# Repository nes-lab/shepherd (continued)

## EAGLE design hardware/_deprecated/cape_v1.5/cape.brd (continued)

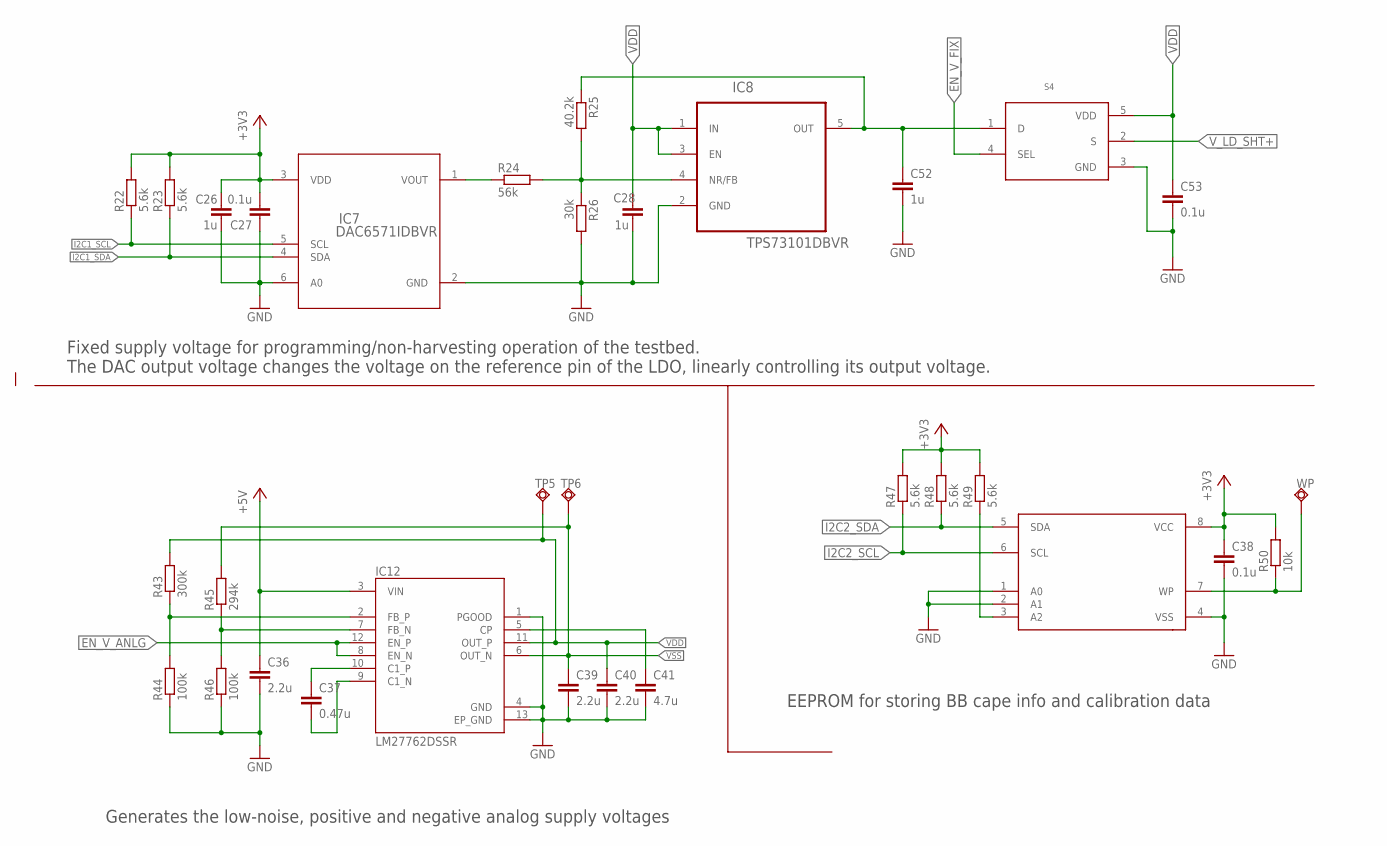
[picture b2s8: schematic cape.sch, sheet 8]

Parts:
C26, C28, C52: 1u; CAPC1608X95
C27, C38, C53: 0.1u; CAPC1005X55
C36, C39, C40: 2.2u; CAPC2012X145
C37: 0.47u; CAPC1608X95
C41: 4.7u; CAPC2012X145
IC7: DAC6571IDBVR
IC8: TPS73101DBVR; SOT95P280X145-5N
IC11: CAT24C256WI-GT3; SO08
IC12: LM27762DSSR; VREG_LM27762DSSR
R22, R23, R47, R48, R49: 5.6k; RESC1005X40
R24: 56k; RESC1005X40
R25: 40.2k; RESC1005X40
R26: 30k; RESC1005X40
R43: 300k; RESC1005X40
R44, R46: 100k; RESC1005X40
R45: 294k; RESC1005X40
R50: 10k; RESC1005X40
S4: TMUX1101DCK; DCK5
TP5, TP6: TPSQTP06R; TP06R
WP: TPSQTP06R; TP06R

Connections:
+3V3: C26.1, C27.2, C38.1, IC7.3 (VDD), IC11.8 (VCC), R22.2, R23.2, R47.2, R48.2, R49.2, R50.2; also elsewhere on the board
+5V: C36.1, IC12.3 (VIN); also elsewhere on the board
EN_V_ANLG: IC12.8 (EN_N), IC12.12 (EN_P); also elsewhere on the board
EN_V_FIX: S4.4 (SEL); also elsewhere on the board
GND: C26.2, C27.1, C28.2, C36.2, C38.2, C39.2, C40.2, C41.2, C52.2, C53.2, IC7.2 (GND), IC7.6 (A0), IC8.2 (GND), IC11.1 (A0), IC11.2 (A1), IC11.4 (VSS), IC12.1 (PGOOD), IC12.4 (GND), IC12.13 (EP_GND), R26.2, R44.1, R46.1, S4.3 (GND); also elsewhere on the board
I2C1_SCL: IC7.5 (SCL), R22.1; also elsewhere on the board
I2C1_SDA: IC7.4 (SDA), R23.1; also elsewhere on the board
I2C2_SCL: IC11.6 (SCL), R47.1; also elsewhere on the board
I2C2_SDA: IC11.5 (SDA), R48.1; also elsewhere on the board
unnamed: C52.1, IC8.5 (OUT), R25.1, S4.1 (D)
unnamed: IC8.4 (NR/FB), R24.2, R25.2, R26.1
unnamed: IC12.2 (FB_P), R43.1, R44.2
unnamed: IC7.1 (VOUT), R24.1
unnamed: IC11.7 (WP), R50.1, WP.TP
unnamed: IC12.7 (FB_N), R45.1, R46.2
unnamed: IC11.3 (A2), R49.1
unnamed: C41.1, IC12.5 (CP)
unnamed: C37.2, IC12.9 (C1_N)
unnamed: C37.1, IC12.10 (C1_P)
VDD: C28.1, C40.1, C53.1, IC8.1 (IN), IC8.3 (EN), IC12.11 (OUT_P), R43.2, S4.5 (VDD), TP5.TP; also elsewhere on the board
VSS: C39.1, IC12.6 (OUT_N), R45.2, TP6.TP; also elsewhere on the board
V_LD_SHT+: S4.2 (S); also elsewhere on the board

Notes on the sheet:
Fixed supply voltage for programming/non-harvesting operation of the testbed. The DAC output voltage changes the voltage on the reference pin of the LDO, linearly controlling its output voltage.
Generates the low-noise, positive and negative analog supply voltages
EEPROM for storing BB cape info and calibration data

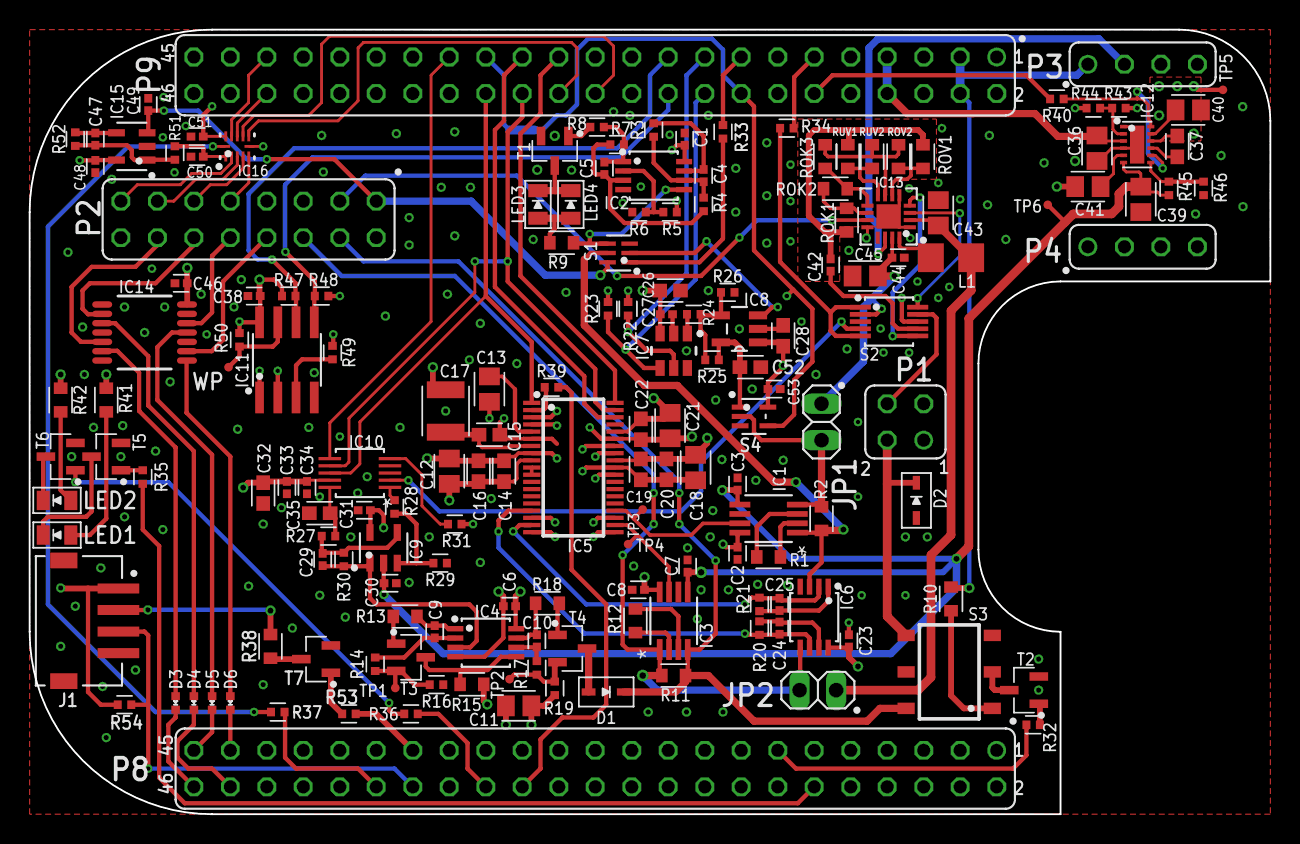
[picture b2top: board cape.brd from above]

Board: 4 copper layers, 86.4 x 54.6 mm, 171 parts (0 on the bottom side), 134 nets.

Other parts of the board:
U$1, U$2, U$3: REFMARK

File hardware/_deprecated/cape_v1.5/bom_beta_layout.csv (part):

"BILL OF MATERIAL WITH BETA STOCK, GROUPED BY VALUES, AS OF 09.10.2015",,,,,,,,,,,,,,,,,,
Part,Value,Device,Package,Description,Description2,Qty,Place_YES/NO,Povided_by_customer_YES/NO,Distributor,Ordernumber,Weblink,Remarks_customer,Unit_price,Total_price,REMARKS_BETA,OPTION1,OPTION2,OPTION3
"C1, C2, C3, C6, C7, C8, C23, C27, C30, C31, C38, C45, C46, C48, C51",0.1u,C_SMD0402,CAPC1005X55, , ,15,YES,NO,Beta,7235228,http://de.rs-online.com/web/p/ceramic-multilayer-capacitors/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, , , , , , ,
"C4, C5, C9, C24, C25, C29, C33, C34, C47, C49",1n,C_SMD0402,CAPC1005X55, , ,10,YES,NO,Beta,147566,http://de.rs-online.com/web/p/keramik-multilayer-kondensator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, , , , , , ,
C10,2.2n,C_SMD0402,CAPC1005X55, , ,1,YES,NO,Digi-Key,399-3068-1-ND,https://www.digikey.com/products/en?keywords=399-3068-1-ND, , , , , , ,
"C11, C12, C13, C18, C21",10u,C_SMD0805,CAPC2012X145, , ,5,YES,NO,Beta,6911161P,http://uk.rs-online.com/web/search/searchBrowseAction.html?m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, , , , , , ,
"C14, C15, C16, C19, C20, C22, C26, C28, C32, C35",1u,C_SMD0603,CAPC1608X95, , ,10,YES,NO,Beta,6911142,http://de.rs-online.com/web/p/keramik-multilayer-kondensator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, , , , , , ,
C17,22u,C_SMD1210,CAPC3225X280, , ,1,YES,NO,Digi-Key,399-7451-1-ND,https://www.digikey.com/products/en?keywords=399-7451-1-ND, , , , , , ,
"C36, C39, C40",2.2u,C_SMD0805,CAPC2012X145, , ,3,YES,NO,Digi-Key,1276-2956-1-ND,https://www.digikey.com/products/en?keywords=1276-2956-1-ND, , , , , , ,
C37,0.47u,C_SMD0603,CAPC1608X95, , ,1,YES,NO,Digi-Key,399-7934-1-ND,https://www.digikey.com/products/en?keywords=399-7934-1-ND, , , , , , ,
"C41, C43, C44",4.7u,C_SMD0805,CAPC2012X145, , ,3,YES,NO,Beta,6911186P,http://uk.rs-online.com/web/search/searchBrowseAction.html?m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, , , , , , ,
"C42, C50",10n,C_SMD0402,CAPC1005X55, , ,2,YES,NO,Beta,147049,http://de.rs-online.com/web/p/keramik-multilayer-kondensator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, , , , , , ,
"D1, D2",BAT43WS-HE3SOD-323,BAT43WS-HE3SOD-323,SOD2513X110, , ,2,YES,NO,Digi-Key,BAT43WS-HE3-08GICT-ND,https://www.digikey.com/products/en?keywords=BAT43WS-HE3-08GICT-ND, , , , , , ,
D3,BZX384B5V1,BZX384B5V1,SOD2513X110, , ,1,YES,NO,Digi-Key,BZX384C5V1-HE3-08GICT-ND,https://www.digikey.com/products/en?keywords=BZX384C5V1-HE3-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, , , , , , ,
"D4, D5, D6, D7",ACDBQC0130L-HF0402,ACDBQC0130L-HF0402,DIOC0905X50N, , ,4,YES,NO,Digi-Key,641-2041-1-ND,https://www.digikey.com/products/en?keywords=641-2041-1-ND, , , , , , ,
"IC1, IC3",AD8422BRMZ,AD8422BRMZ,RM_8-L, , ,2,YES,NO,Digi-Key,AD8422ARMZ-ND,https://www.digikey.com/products/en?keywords=AD8422ARMZ-ND, , , , , , ,
"IC2, IC4, IC6",OPA2388DGK8_L,OPA2388DGK8_L,DGK8-L, , ,3,YES,NO,Digi-Key,296-50277-1-ND,https://www.digikey.com/products/en?keywords=296-50277-1-ND, , , , , , ,
IC5,ADS8694TSSOP38,ADS8694TSSOP38,TSSOP38, , ,1,YES,NO,Digi-Key,296-42531-5-ND,https://www.digikey.com/products/en?keywords=296-42531-5-ND, , , , , , ,
IC7,DAC6571IDBVR,DAC6571IDBVR,DAC6571IDBVR, , ,1,YES,NO,Digi-Key,296-48525-1-ND,https://www.digikey.com/products/en?keywords=296-48525-1-ND, , , , , , ,
IC8,TPS73101DBVR,TPS73101DBVR,SOT95P280X145-5N,"Cap-Free, NMOS, 400mA Low-Dropout Regulator with Reverse Current Protection", ,1,YES,NO,Digi-Key,296-27058-1-ND,https://www.digikey.com/products/en?keywords=296-27058-1-ND, , , , , , ,
"IC9, IC15",LMP7701MF,LMP7701MF,DBV5-L, , ,2,YES,NO,Digi-Key,LMP7701MF/NOPBCT-ND,https://www.digikey.com/products/en?keywords=LMP7701MF/NOPBCT-ND, , , , , , ,
IC10,DAC8562_DGS_10,DAC8562_DGS_10,DGS10, , ,1,YES,NO,Digi-Key,296-43693-1-ND,https://www.digikey.com/products/en?keywords=296-43693-1-ND, , , , , , ,
IC11,CAT24C256WI-GT3,CAT24C256WI-GT3,SO08, , ,1,YES,NO,Digi-Key,CAT24C256WI-GT3OSCT-ND,https://www.digikey.com/products/en?keywords=CAT24C256WI-GT3OSCT-ND, , , , , , ,
IC12,LM27762DSSR,LM27762DSSR,VREG_LM27762DSSR,Low-Noise Positive- and Negative-Output Charge Pump With Integrated LDO 12-WSON -40 to 85, ,1,YES,NO,Digi-Key,296-44944-1-ND,https://www.digikey.com/products/en?keywords=296-44944-1-ND, , , , , , ,
IC13,BQ25504_RGT_16,BQ25504_RGT_16,RGT16_1P7X1P7, , ,1,YES,NO,Digi-Key,296-29741-1-ND,https://www.digikey.com/products/en?keywords=296-29741-1-ND, , , , , , ,
IC14,SN74LV4T125PWR,SN74LV4T125PWR,PW0014A_N, , ,1,YES,NO,Digi-Key,296-40545-1-ND,https://www.digikey.com/products/en?keywords=296-40545-1-ND, , , , , , ,
IC16,TXB0304RUTR,TXB0304RUTR,RUT0012A, , ,1,YES,NO,Digi-Key,296-29682-1-ND,https://www.digikey.com/products/en?keywords=296-29682-1-ND, , , , , , ,
"JP1, JP2", ,PINHD-1X2,1X02,PIN HEADER, ,2,YES,NO,Digi-Key,732-5315-ND,https://www.digikey.com/products/en?keywords=732-5315-ND, , , , , , ,
K1,G3VM-31HR22SOP,G3VM-31HR22SOP,SOP06,PhotoMOS Relay NAiS, ,1,YES,NO,Digi-Key,Z8598-ND,https://www.digikey.com/products/en?keywords=Z8598-ND, , , , , , ,
L1,22u,L-EUL3225P,L3225P,"INDUCTOR, European symbol", ,1,YES,NO,Digi-Key,732-7315-1-ND,https://www.digikey.com/products/en?keywords=732-7315-1-ND, , , , , , ,
"LED1, LED2, LED3, LED4",598-8130-107FLED_0805,598-8130-107FLED_0805,LEDC2012X75, , ,4,YES,NO,Digi-Key,350-2040-1-ND,https://www.digikey.com/products/en?keywords=350-2040-1-ND, , , , , , ,
P1, ,FE02-2,FE02-2,FEMALE HEADER, ,1,YES,NO,Digi-Key,SAM1212-02-ND,https://www.digikey.com/products/en?keywords=SAM1212-02-ND, , , , , , ,
P2, ,FE08-2,FE08-2,FEMALE HEADER, ,1,YES,NO,Digi-Key,SAM1212-08-ND,https://www.digikey.com/products/en?keywords=SAM1212-08-ND, , , , , , ,
"P3, P4", ,FE04-1,FE04-1,FEMALE HEADER, ,2,YES,NO,Digi-Key,SAM1213-04-ND,https://www.digikey.com/products/en?keywords=SAM1213-04-ND, , , , , , ,
"P8, P9", ,FE23-2,FE23-2,FEMALE HEADER, ,2,YES,NO,Digi-Key,SAM1204-23-ND ,https://www.digikey.com/products/en?keywords=SAM1204-23-ND, , , , , , ,
"R1, R12, R15",402,R_SMD0603,RESC1608X55, , ,3,YES,NO,Digi-Key,P19926CT-ND,https://www.digikey.com/products/en?keywords=P19926CT-ND, , , , , , ,
"R2, R11",2,R_SMD0603,RESC1608X55, , ,2,YES,NO,Digi-Key,A102258CT-ND,https://www.digikey.com/products/en?keywords=A102258CT-ND, , , , , , ,
"R3, R20, R21, R51",24,R_SMD0402,RESC1005X40, , ,4,YES,NO,Digi-Key,YAG3073CT-ND,https://www.digikey.com/products/en?keywords=YAG3073CT-ND, , , , , , ,
R4,2.4k,R_SMD0402,RESC1005X40, , ,1,YES,NO,Digi-Key,311-2.40KLRCT-ND,https://www.digikey.com/products/en?keywords=311-2.40KLRCT-ND, , , , , , ,
R5,3.6k,R_SMD0402,RESC1005X40, , ,1,YES,NO,Digi-Key,311-3.6KLRCT-ND,https://www.digikey.com/products/en?keywords=311-3.6KLRCT-ND, , , , , , ,
"R6, R7, R14, R17, R31, R50, R52",10k,R_SMD0402,RESC1005X40, , ,7,YES,NO,Beta,618-5832,http://de.rs-online.com/web/p/products/6185832/?searchTerm=6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, , , , , , ,
"R8, R16, R28, R30",1.2k,R_SMD0402,RESC1005X40, , ,4,YES,NO,Beta,618-6138,http://de.rs-online.com/web/p/products/6186138/?searchTerm=6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, , , , , , ,
R9,91,R_SMD0603,RESC1608X55, , ,1,YES,NO,Digi-Key,311-91.0HRCT-ND,https://www.digikey.com/products/en?keywords=311-91.0HRCT-ND, , , , , , ,
"R10, R13, R18, R41, R42",220,R_SMD0603,RESC1608X55, , ,5,YES,NO,Beta,6979191,http://uk.rs-online.com/web/search/searchBrowseAction.html?m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, , , , , , ,
R19,30,R_SMD0402,RESC1005X40, , ,1,YES,NO,Digi-Key,A102788CT-ND,https://www.digikey.com/products/en?keywords=A102788CT-ND, , , , , , ,
"R22, R23, R47, R48, R49",5.6k,R_SMD0402,RESC1005X40, , ,5,YES,NO,Beta,698-0693,http://de.rs-online.com/web/p/products/6980693/?searchTerm=6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, , , , , , ,
R24,56k,R_SMD0402,RESC1005X40, , ,1,YES,NO,Beta,698-6761,http://de.rs-online.com/web/p/products/6986761/?searchTerm=6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, , , , , , ,
R25,40.2k,R_SMD0402,RESC1005X40, , ,1,YES,NO,Digi-Key,311-40.2KLRCT-ND,https://www.digikey.com/products/en?keywords=311-40.2KLRCT-ND, , , , , , ,
R26,30k,R_SMD0402,RESC1005X40, , ,1,YES,NO,Digi-Key,311-30.0KLRCT-ND,https://www.digikey.com/products/en?keywords=311-30.0KLRCT-ND, , , , , , ,
"R27, R29, R44, R46",100k,R_SMD0402,RESC1005X40, , ,4,YES,NO,Beta,6986783,http://uk.rs-online.com/web/search/searchBrowseAction.html?m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, , , , , , ,
"R32, R33, R34, R35, R36, R37, R38, R39, R40",510,R_SMD0402,RESC1005X40, , ,9,YES,NO,Beta,698-0599,http://de.rs-online.com/web/p/smd-widerstande/6980599/?searc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, , , , , , ,
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
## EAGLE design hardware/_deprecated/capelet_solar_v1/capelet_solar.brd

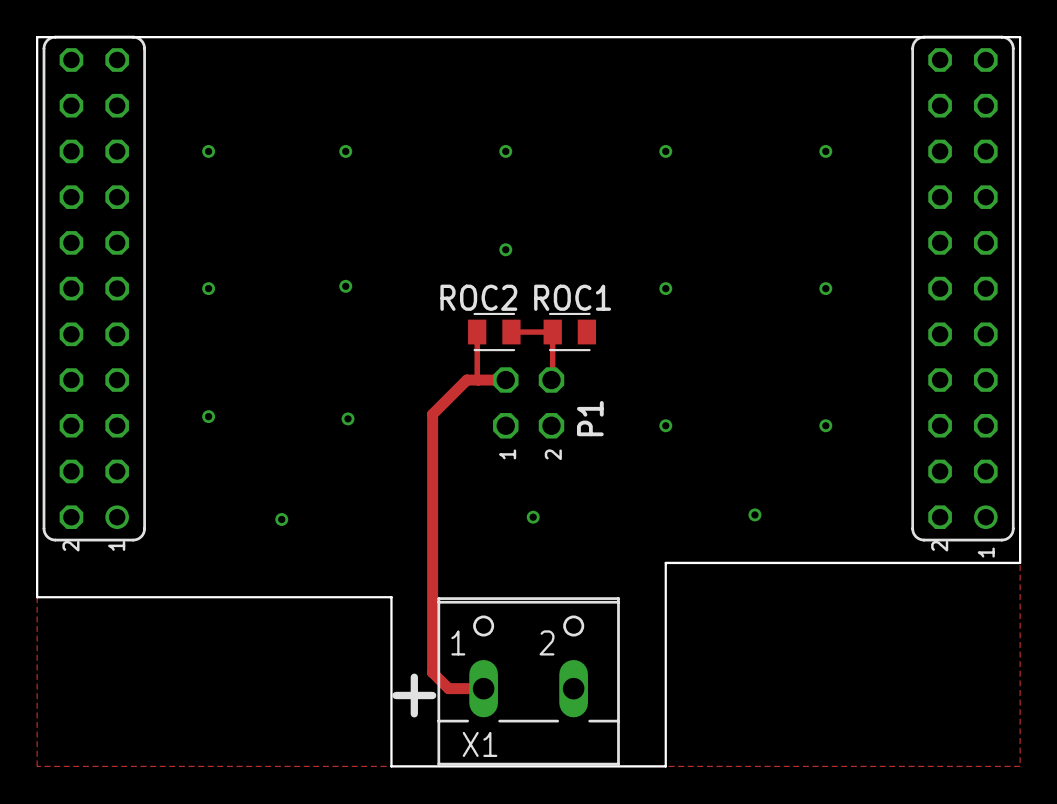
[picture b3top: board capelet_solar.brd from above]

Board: 2 copper layers, 54.6 x 40.5 mm, 7 parts (1 on the bottom side), 3 nets.

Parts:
P1: 2X02
P8, P9: FE11-2
ROC1: 8M; RESC2012X65
ROC2: 2M; RESC2012X65
U$1: SHPRD_CPLT_H
X1: W237-102

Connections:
GND: P1.1, P1.2, ROC1.1, X1.2
unnamed: P1.3, ROC2.2, X1.1
unnamed: P1.4, ROC1.2, ROC2.1

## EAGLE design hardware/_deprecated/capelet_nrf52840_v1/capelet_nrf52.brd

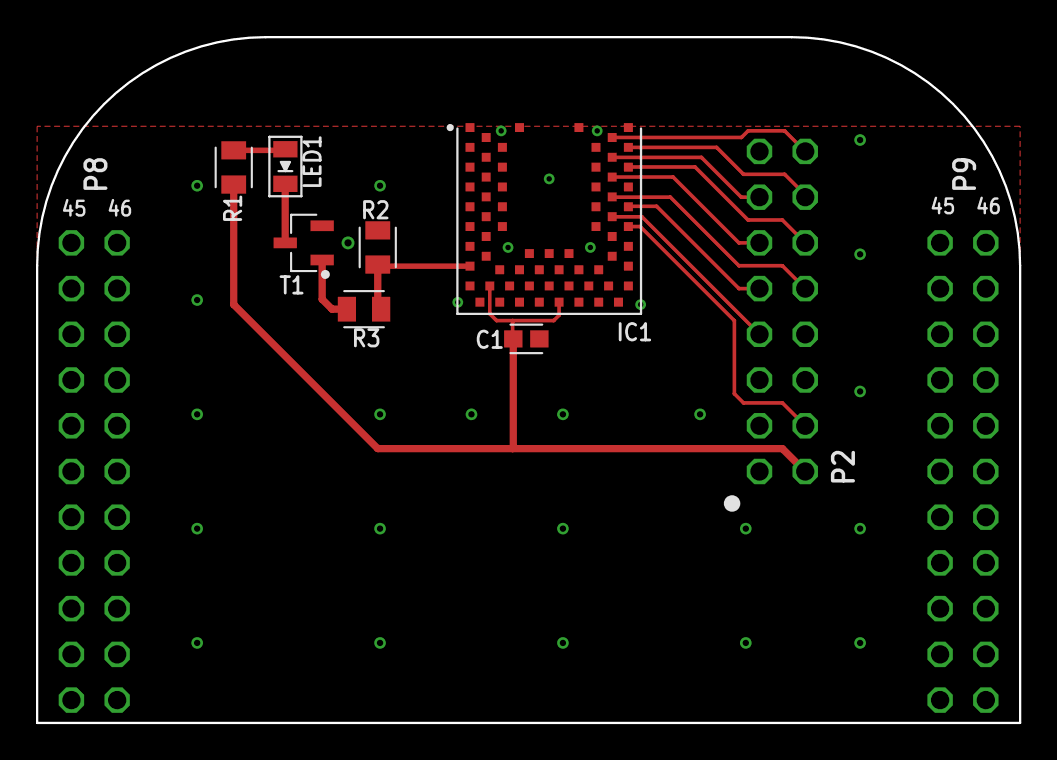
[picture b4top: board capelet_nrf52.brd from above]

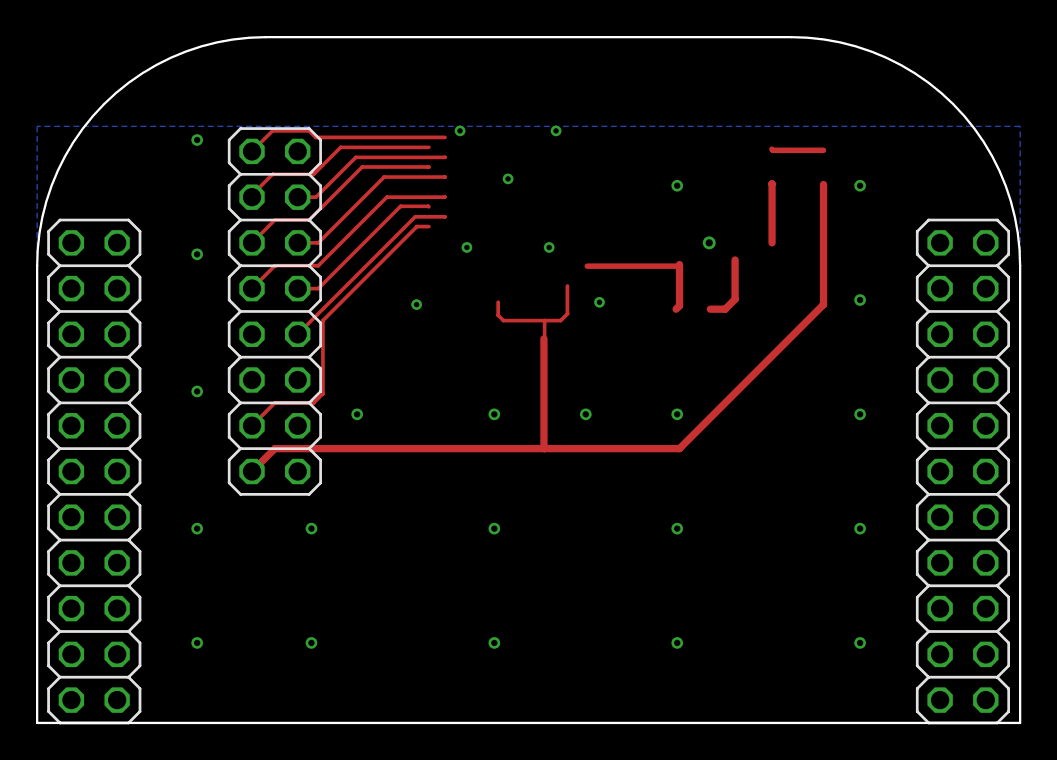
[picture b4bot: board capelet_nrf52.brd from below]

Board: 2 copper layers, 54.6 x 38.1 mm, 11 parts (3 on the bottom side), 15 nets.

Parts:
C1: 4.7u; CAPC1608X95
IC1: BMD-340-A-R; RIGADO_BMD-340-A-R
LED1: 598-8130-107FLED_0805; LEDC2012X75
P2: 2X08
P8, P9: 2X11
R1, R3: 130R; RESC2012X65
R2: 10k; RESC2012X65
T1: SI2374DSSOT23-VSHAY; SOT95P237X112-3
U$3: SHPRD_CPLT_T

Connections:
GND: C1.2, IC1.1, IC1.2, IC1.3, IC1.4, IC1.5, IC1.16, IC1.18, IC1.29, IC1.30, IC1.45, IC1.46, IC1.47, IC1.55, P2.1, P2.8, P2.15, R2.2, T1.2
GPIO0: IC1.37, P2.9
GPIO1: IC1.42, P2.13
GPIO2: IC1.36, P2.7
GPIO3: IC1.40, P2.11
GPIO_LED: IC1.15, R2.1, R3.1
unnamed: R3.2, T1.1
unnamed: LED1.1, T1.3
unnamed: LED1.2, R1.1
SWDCLK: IC1.43, P2.14
SWDIO: IC1.44, P2.16
UART_RX: IC1.41, P2.12
UART_TX: IC1.38, P2.10
V_BATOK: IC1.35, P2.4
V_SUP: C1.1, IC1.17, IC1.65, P2.2, R1.2

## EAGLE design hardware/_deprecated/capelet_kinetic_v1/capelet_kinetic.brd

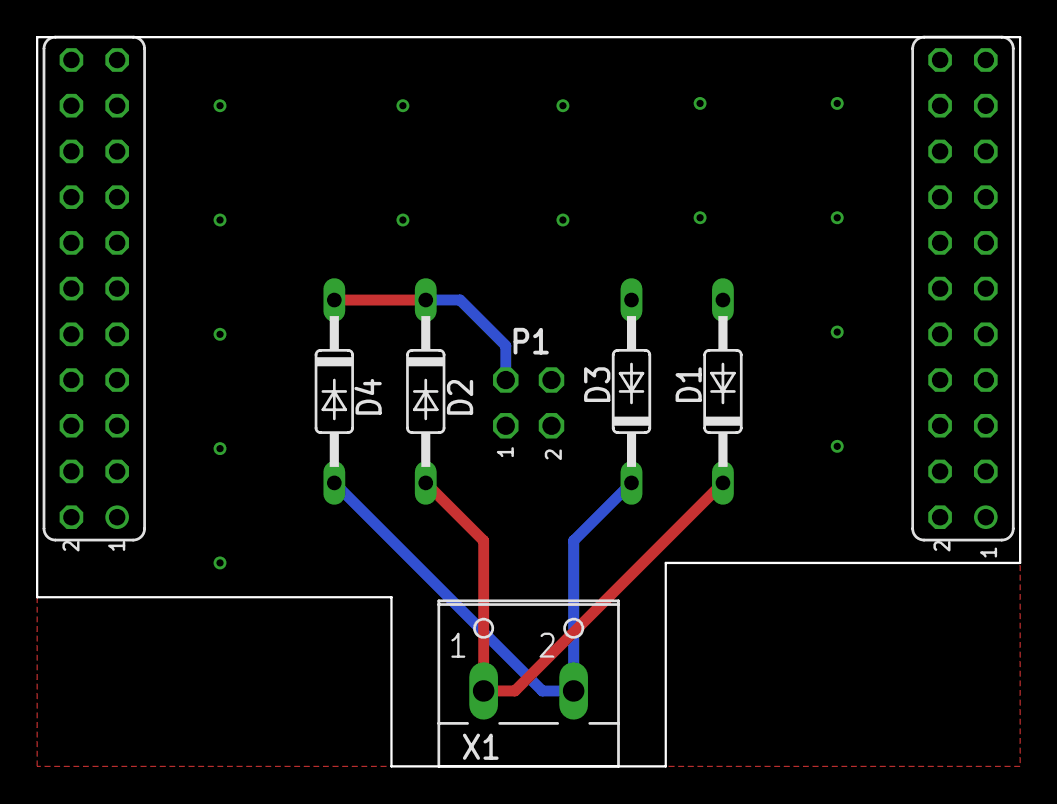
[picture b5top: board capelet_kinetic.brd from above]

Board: 2 copper layers, 54.6 x 40.5 mm, 9 parts (1 on the bottom side), 4 nets.

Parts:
D1, D2, D3, D4: BAT42; DO35-10
P1: 2X02
P8, P9: FE11-2
U$1: SHPRD_CPLT_H
X1: W237-102

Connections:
GND: D1.A, D3.A, P1.1, P1.2
unnamed: D1.C, D2.A, X1.1
unnamed: D3.C, D4.A, X1.2
V_H: D2.C, D4.C, P1.3

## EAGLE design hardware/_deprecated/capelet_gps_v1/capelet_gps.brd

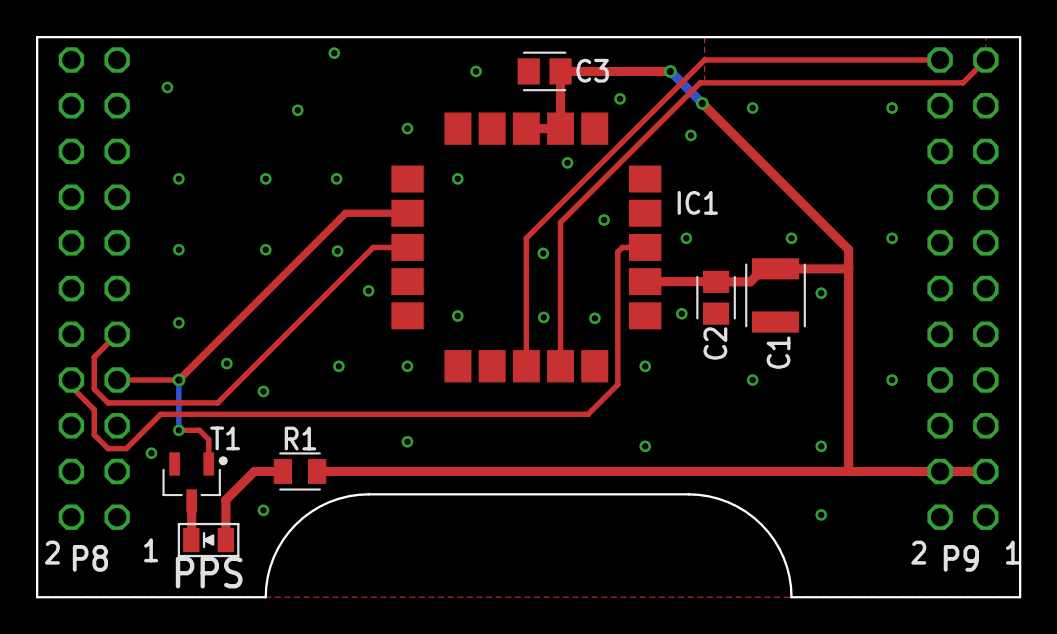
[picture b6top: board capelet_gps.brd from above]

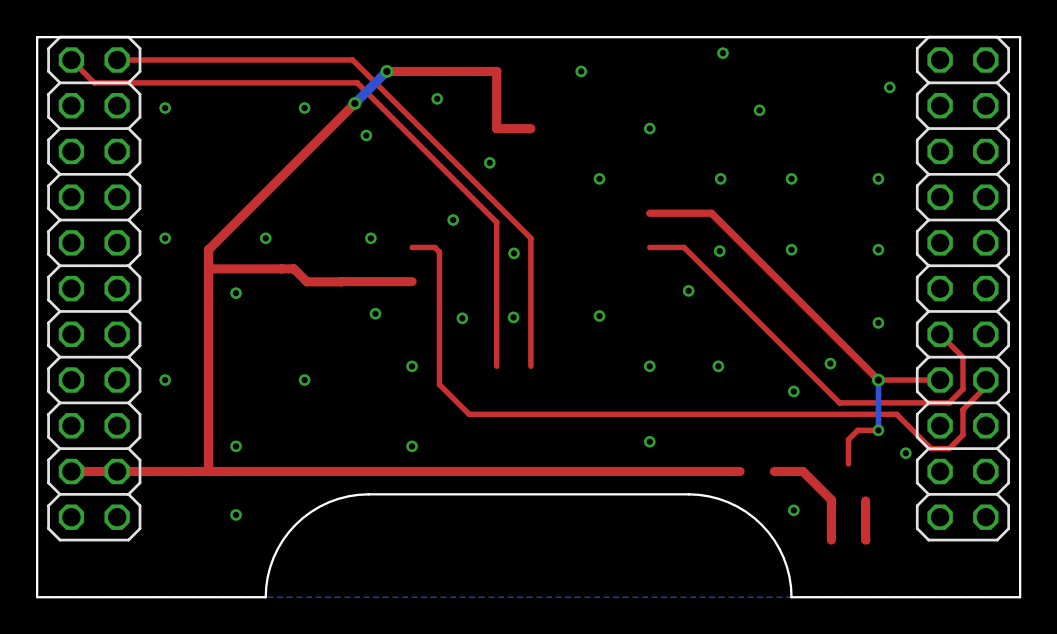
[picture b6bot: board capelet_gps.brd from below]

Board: 2 copper layers, 54.6 x 31.1 mm, 13 parts (2 on the bottom side), 9 nets.

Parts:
C1: 22u; CAPC3225X280
C2, C3: 0.1u; CAPC2012X145
IC1: SAM-M8Q
P8, P9: 2X11
PPS: 598-8130-107FLED_0805; LEDC2012X75
R1: 130R; RESC2012X65
T1: SI2374DSSOT23-VSHAY; SOT95P237X112-3
U$1, U$2, U$4: REFMARK
U$3: SHPRD_CPLT_G

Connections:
+3V3: C1.1, C2.1, C3.1, IC1.2, IC1.3, IC1.17, P9.3, P9.4, R1.2
GND: C1.2, C2.2, C3.2, IC1.1, IC1.4, IC1.5, IC1.6, IC1.10, IC1.11, IC1.15, IC1.16, IC1.20, P8.1, P8.2, P9.1, P9.2, T1.2
unnamed: PPS.1, T1.3
unnamed: PPS.2, R1.1
RESET_N: IC1.18, P8.8
SAFEBOOT_N: IC1.8, P8.9
TIMEPULSE: IC1.7, P8.7, T1.1
UART2_RX: IC1.13, P9.22
UART2_TX: IC1.14, P9.21

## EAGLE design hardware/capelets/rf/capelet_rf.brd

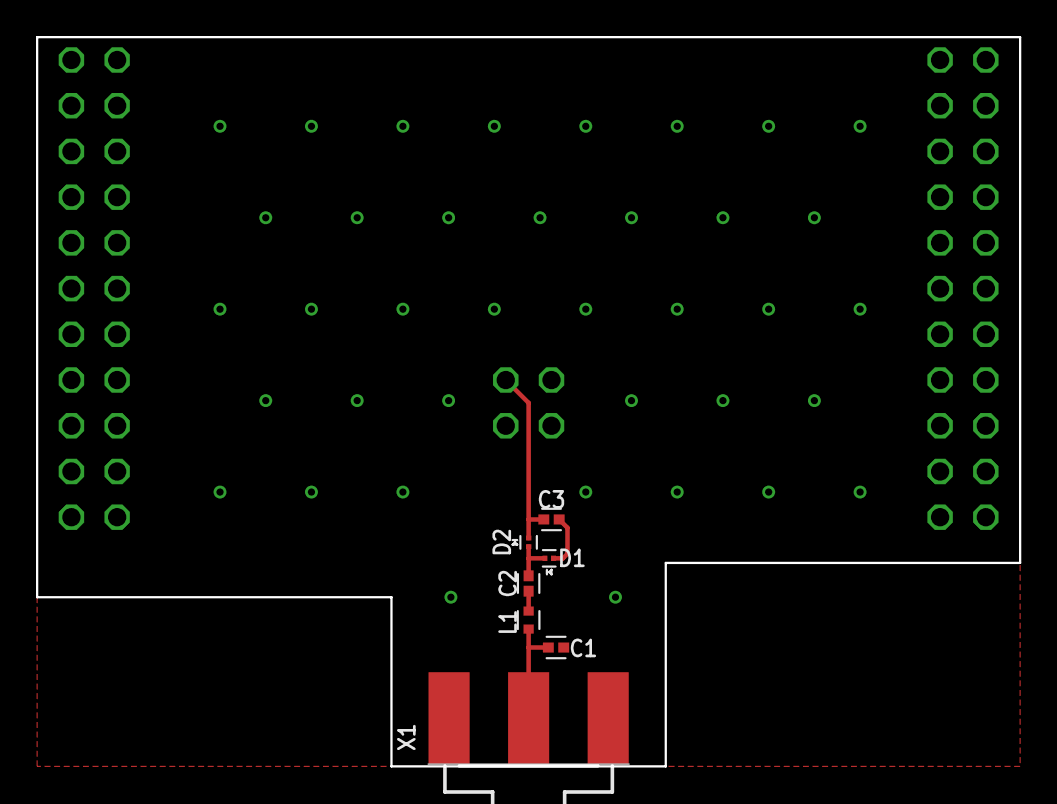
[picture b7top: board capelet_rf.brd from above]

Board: 2 copper layers, 54.6 x 40.5 mm, 8 parts (0 on the bottom side), 8 nets.

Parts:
C1, C2, C3: CAPC1005X55
D1, D2: SMS7630-0610201; DIOC0502X27N
L1: 0402HM-6N8EGTS0402; INDC1004X60N
X1: SMA-142-0701-801/806; J502-ND-142-0701-801/806
Y1: SHPRD_CPLT_H

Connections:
+3V3: Y1.P9$3, Y1.P9$4
GND: C1.1, C3.1, D1.1, X1.G@1, X1.G@2, X1.G@3, X1.G@4, Y1.P1$1, Y1.P1$3, Y1.P8$1, Y1.P8$2, Y1.P9$1, Y1.P9$2
unnamed: C2.2, D1.2, D2.1
unnamed: C1.2, L1.1, X1.1
unnamed: C2.1, L1.2
SYS_5V: Y1.P9$7, Y1.P9$8
VDD_5V: Y1.P9$5, Y1.P9$6
V_H: C3.2, D2.2, Y1.P1$2

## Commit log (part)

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2026-05-19 update tooling
2026-05-19 bump version
2026-05-19 switch to gnupru 2026.05 - GCC 16.1
2026-05-19 repair unittests
2026-05-21 reliability-booster for pru-programmer
2026-06-02 ⬆ Update pydantic requirement from >=2.13.3 to >=2.13.4
    Updates the requirements on [pydantic](https://github.com/pydantic/pydantic) to permit the latest version.
    - [Release notes](https://github.com/pydantic/pydantic/releases)
    - [Changelog](https://github.com/pydantic/pydantic/blob/main/HISTORY.md)
    - [Commits](https://github.com/pydantic/pydantic/compare/v2.13.3...v2.13.4)
    ---
    updated-dependencies:
2026-06-02 ⬆ Bump software/shepherd-tools from `a29b74d` to `8dddc5a`
    Bumps [software/shepherd-tools](https://github.com/nes-lab/shepherd-tools) from `a29b74d` to `8dddc5a`.
    - [Release notes](https://github.com/nes-lab/shepherd-tools/releases)
    - [Commits](https://github.com/nes-lab/shepherd-tools/compare/a29b74db35d86beb31248c21811e6a07e730ff6d...8dddc5a28d09d0cf1d18051ab4539249ed0632f9)
    ---
    updated-dependencies:
    - dependency-name: software/shepherd-tools
2026-06-05 cleaner exit on already misbehaving sheep-routines
2026-06-05 ID-patching now informs if it skips & shorten programmer error-counter before failing
2026-06-05 kMod -> fix last Phandle-leak
2026-06-05 refactor cleanup of platform data and remove another leak of phandles
2026-06-05 small doc additions
2026-06-09 prep release
2026-06-18 kMod - inform about buffer-specs in DRAM
2026-06-18 split up the buffer DRAM allocation into 4 parts
2026-06-18 Device-tree - add memory reserve for later kernels
2026-06-18 update changelog
2026-06-18 typo
2026-06-18 sheep - add bson-package as default
2026-06-18 integrate internet-watchdog into observer-role
2026-06-18 move bson-install to observer-role
2026-06-18 refactor observer-role
2026-06-23 kMod - warn about mismatch in buffer-size
2026-06-23 update openOCD-config
2026-06-24 rename files of pru-programmer
2026-06-24 programmer - let sbw use static delay
2026-06-24 bring in changes from riotee-sbw-transport
2026-06-24 bring in changes from riotee-sbw-jtag
2026-06-25 bring in changes from riotee-sbw-device
2026-06-25 improve sub-states of programmer
2026-06-26 sheep - implement ocd-programmer
2026-06-26 optimize & test ocd-programmer
2026-06-29 fix unittests
2026-06-29 kmod - improve info about buffers
2026-06-29 uboot - increase CMA and activate fsck on boot
2026-06-29 bump ver
2026-06-29 make pytest use /tmp less
